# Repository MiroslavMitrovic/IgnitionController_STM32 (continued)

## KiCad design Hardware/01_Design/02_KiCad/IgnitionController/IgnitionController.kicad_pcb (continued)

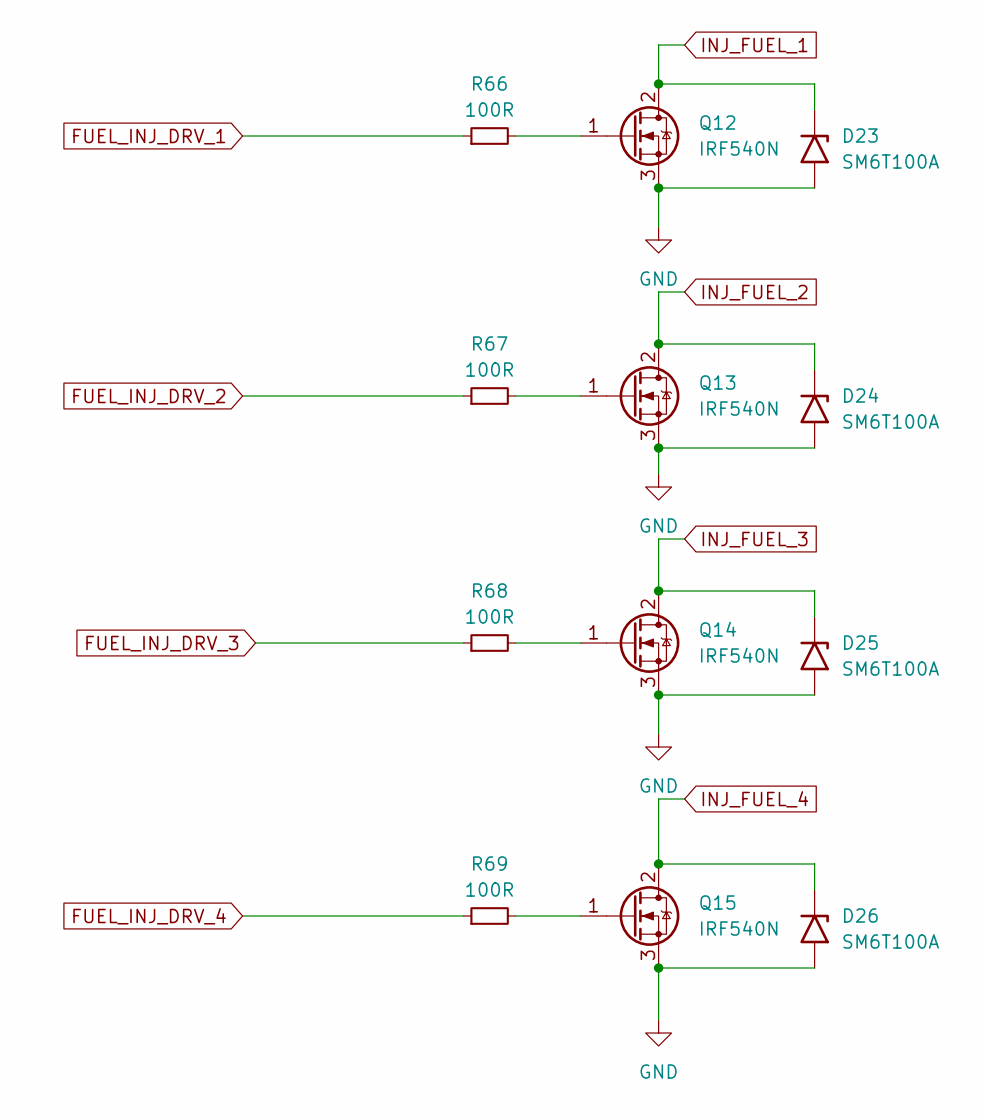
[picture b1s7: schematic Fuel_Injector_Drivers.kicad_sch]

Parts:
D23, D24, D25, D26: SM6T100A; D_SMB
Q12, Q13, Q14, Q15: IRF540N; TO-220-3_Vertical
R66, R67, R68, R69: 100R; R_0603_1608Metric_Pad0.98x0.95mm_HandSolder

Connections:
FUEL_INJ_DRV_1: R66.1; also elsewhere on the board
FUEL_INJ_DRV_2: R67.1
FUEL_INJ_DRV_3: R68.1; also elsewhere on the board
FUEL_INJ_DRV_4: R69.1; also elsewhere on the board
INJ_FUEL_1: D23.1 (A1), Q12.2 (D); also elsewhere on the board
INJ_FUEL_2: D24.1 (A1), Q13.2 (D); also elsewhere on the board
INJ_FUEL_3: D25.1 (A1), Q14.2 (D); also elsewhere on the board
INJ_FUEL_4: D26.1 (A1), Q15.2 (D); also elsewhere on the board
unnamed: Q12.1 (G), R66.2
unnamed: Q13.1 (G), R67.2
unnamed: Q14.1 (G), R68.2
unnamed: Q15.1 (G), R69.2

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
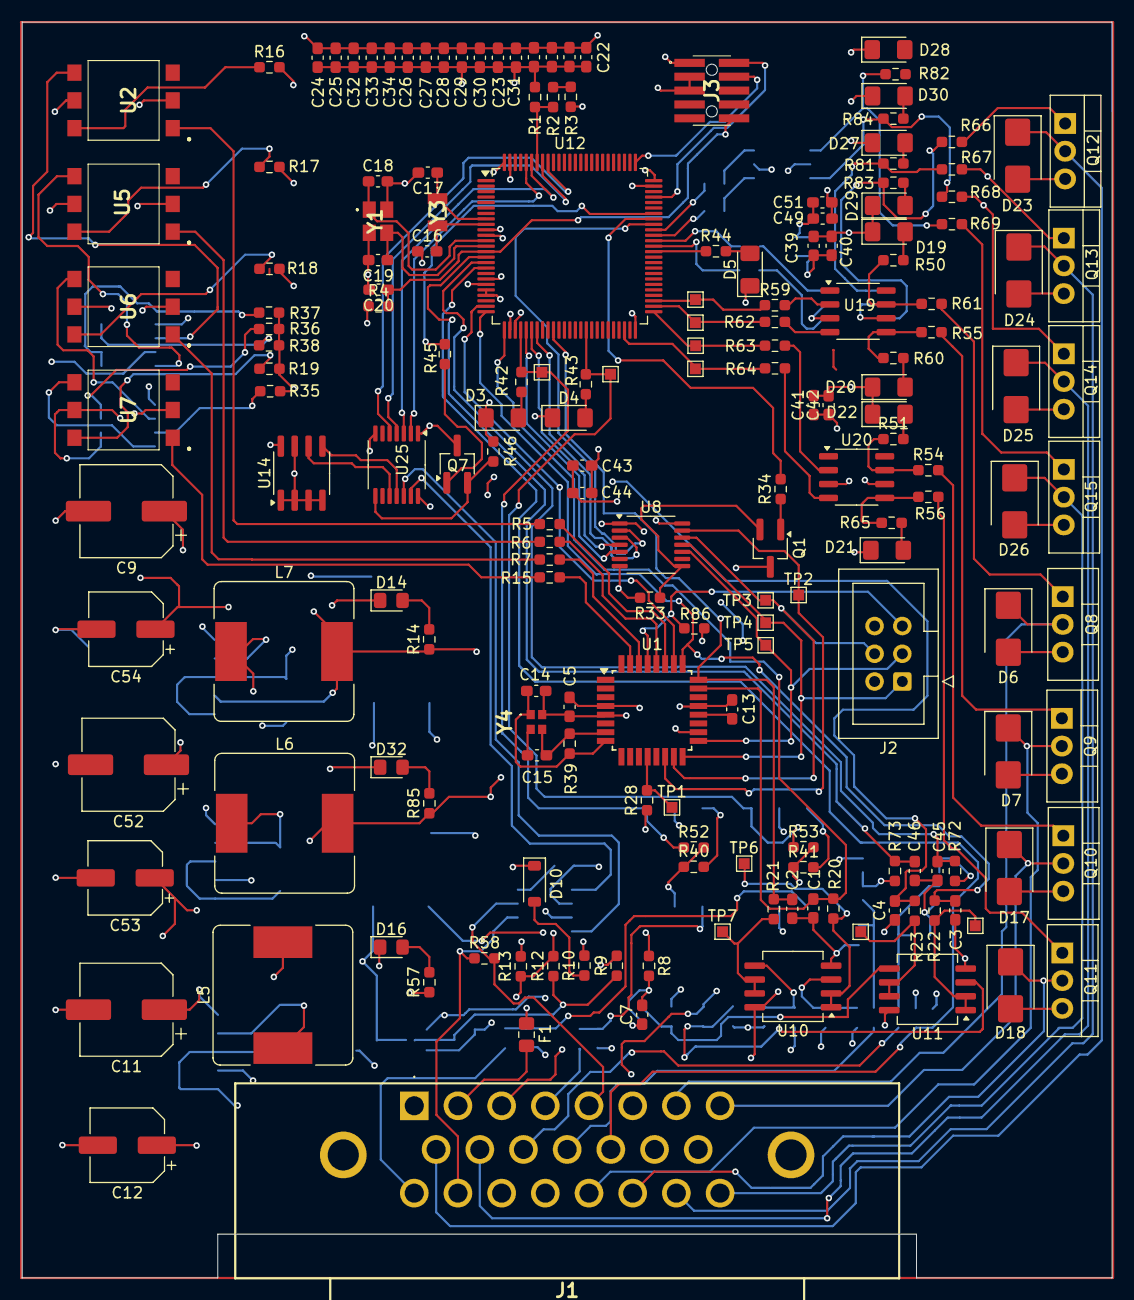
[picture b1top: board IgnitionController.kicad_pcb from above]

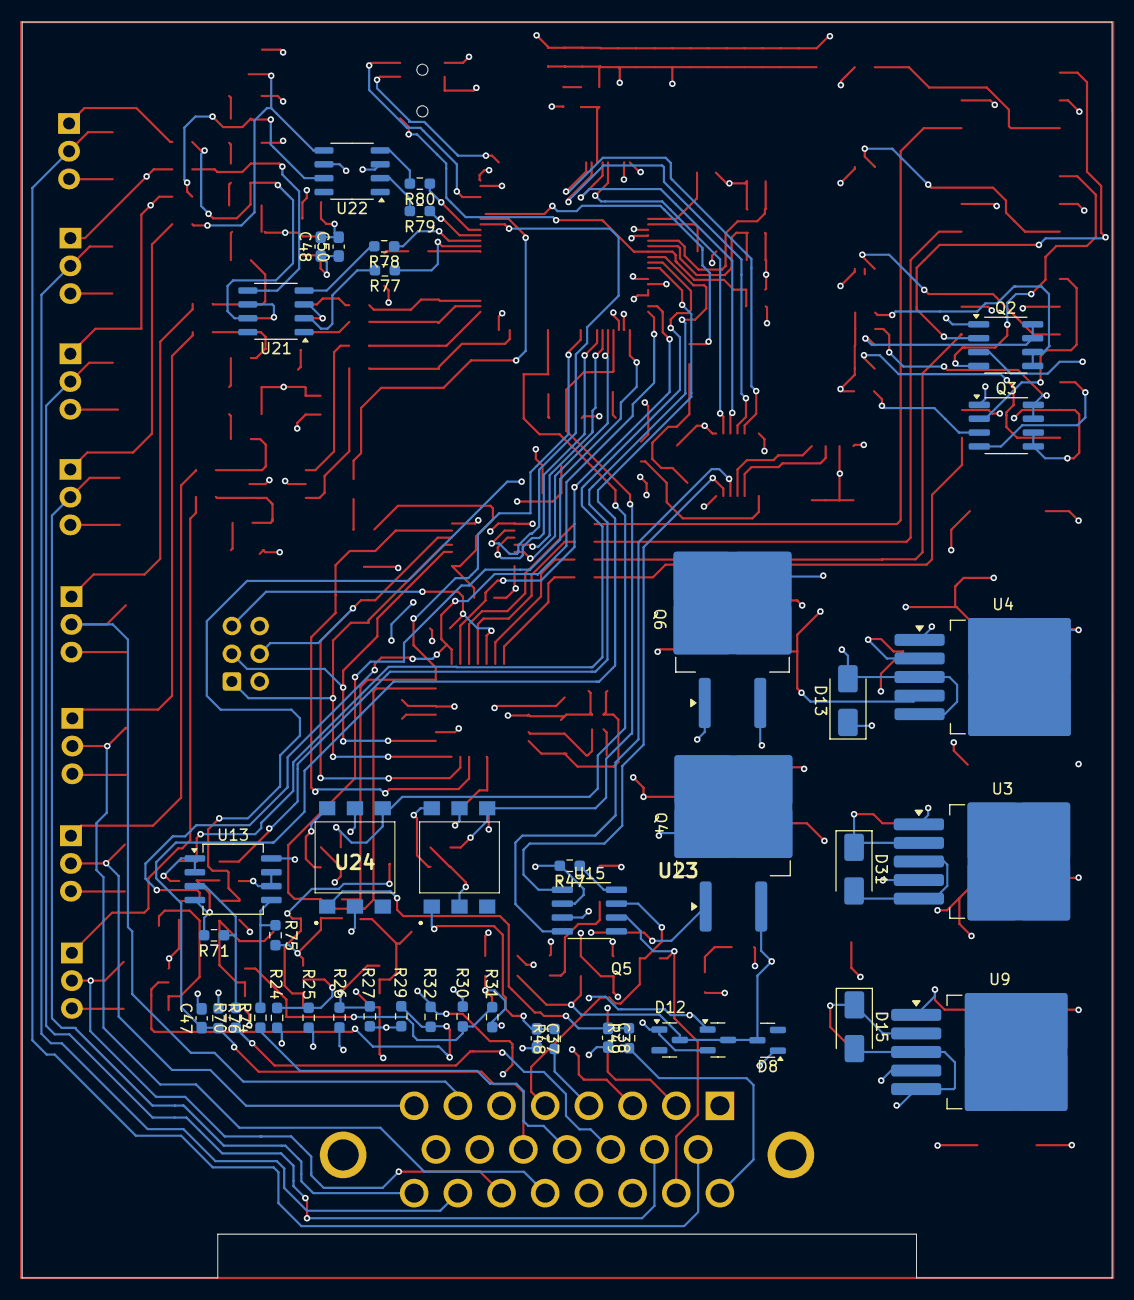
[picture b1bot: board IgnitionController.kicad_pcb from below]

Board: 4 copper layers, 99.8 x 115.0 mm, 226 parts (44 on the bottom side), 159 nets.

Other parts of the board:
R86: 10k; R_0603_1608Metric_Pad0.98x0.95mm_HandSolder
Y4: NX2016SA-16MHZ-EXS00A-CS07826; NX2016SA16MHZEXS00ACS07826

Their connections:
PMIC_RESET: R86.2; also elsewhere on the board
VPMIC: R86.1; also elsewhere on the board

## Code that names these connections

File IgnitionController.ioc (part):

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Mcu.Name=STM32F407V(E-G)Tx
Mcu.Package=LQFP100
Mcu.UserName=STM32F407VGTx
PA1.GPIOParameters=GPIO_Label
PA1.GPIO_Label=ADC_VMCU
PA1.Signal=ADCx_IN1
PA10.GPIOParameters=GPIO_Label
PA10.GPIO_Label=OE_PIN2
PA10.Signal=GPIO_Output
PA13.GPIOParameters=GPIO_Label
PA13.GPIO_Label=SWDIO
PA13.Mode=Serial_Wire
PA13.Signal=SYS_JTMS-SWDIO
PA14.GPIOParameters=GPIO_Label
PA14.GPIO_Label=SWCLK
PA14.Mode=Serial_Wire
PA14.Signal=SYS_JTCK-SWCLK
PA2.GPIOParameters=GPIO_Label
PA2.GPIO_Label=ADC_VSENS
PA2.Signal=ADCx_IN2
PA3.GPIOParameters=GPIO_Label
PA3.GPIO_Label=ADC_VBAT
PA3.Signal=ADCx_IN3
PA4.GPIOParameters=GPIO_PuPd,GPIO_Label
PA4.GPIO_Label=Signal1_IntPin
PA4.GPIO_PuPd=GPIO_PULLDOWN
PA4.Signal=GPXTI4
PA5.Mode=Full_Duplex_Master
PA5.Signal=SPI1_SCK
PA6.Mode=Full_Duplex_Master
PA6.Signal=SPI1_MISO
PA7.Mode=Full_Duplex_Master
PA7.Signal=SPI1_MOSI
PA8.GPIOParameters=GPIO_Label
PA8.GPIO_Label=SPI1_CS
PA8.Signal=GPIO_Output
PA9.GPIOParameters=GPIO_Label
PA9.GPIO_Label=OE_PIN1
PA9.Signal=GPIO_Output
PB0.GPIOParameters=GPIO_Label
PB0.GPIO_Label=ADC_IGNITION
PB0.Signal=ADCx_IN8
PB11.GPIOParameters=GPIO_Label
PB11.GPIO_Label=Cylinder4Out_Pin
PB11.Signal=GPIO_Output
PB12.GPIOParameters=GPIO_Label
PB12.GPIO_Label=Cylinder3Out_Pin
PB12.Signal=GPIO_Output
PB13.GPIOParameters=GPIO_Label
PB13.GPIO_Label=TestLED2
PB13.Signal=GPIO_Output
PB14.GPIOParameters=GPIO_Label
PB14.GPIO_Label=TestLED1
PB14.Signal=GPIO_Output
PB6.Mode=I2C
PB6.Signal=I2C1_SCL
PB7.Mode=I2C
PB7.Signal=I2C1_SDA
PB8.Mode=CAN_Activate
PB8.Signal=CAN1_RX
PB9.Mode=CAN_Activate
PB9.Signal=CAN1_TX
PC0.Signal=ADCx_IN10
PC1.Signal=ADCx_IN11
PC10.Mode=Asynchronous
PC10.Signal=USART3_TX
PC11.Mode=Asynchronous
PC11.Signal=USART3_RX
PC14-OSC32_IN.GPIOParameters=GPIO_Label
PC14-OSC32_IN.GPIO_Label=PC14-OSC32_IN
PC14-OSC32_IN.Mode=LSE-External-Oscillator
PC14-OSC32_IN.Signal=RCC_OSC32_IN
PC15-OSC32_OUT.GPIOParameters=GPIO_Label
PC15-OSC32_OUT.GPIO_Label=PC15-OSC32_OUT
PC15-OSC32_OUT.Mode=LSE-External-Oscillator
PC15-OSC32_OUT.Signal=RCC_OSC32_OUT
PC2.Signal=ADCx_IN12
PC6.Signal=S_TIM3_CH1
PC7.Signal=S_TIM3_CH2
PC8.Signal=S_TIM3_CH3
PC9.Signal=S_TIM3_CH4
PE10.GPIOParameters=GPIO_PuPd,GPIO_Label
PE10.GPIO_Label=Signal2_IntPin
PE10.GPIO_PuPd=GPIO_PULLDOWN
PE10.Signal=GPXTI10
PH0-OSC_IN.GPIOParameters=GPIO_Label
PH0-OSC_IN.GPIO_Label=PH0-OSC_IN
PH0-OSC_IN.Mode=HSE-External-Oscillator
PH0-OSC_IN.Signal=RCC_OSC_IN
PH1-OSC_OUT.GPIOParameters=GPIO_Label
PH1-OSC_OUT.GPIO_Label=PH1-OSC_OUT
PH1-OSC_OUT.Mode=HSE-External-Oscillator
PH1-OSC_OUT.Signal=RCC_OSC_OUT
RCC.HSE_VALUE=8000000
RCC.SYSCLKFreq_VALUE=168000000
RCC.SYSCLKSource=RCC_SYSCLKSOURCE_PLLCLK
board=STM32F407G-DISC1
boardIOC=true

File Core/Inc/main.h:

/* USER CODE BEGIN Header */
/**
  ******************************************************************************
  * @file           : main.h
  * @brief          : Header for main.c file.
  *                   This file contains the common defines of the application.
  ******************************************************************************
  * @attention
  *
  * Copyright (c) 2022 STMicroelectronics.
  * All rights reserved.
  *
  * This software is licensed under terms that can be found in the LICENSE file
  * in the root directory of this software component.
  * If no LICENSE file comes with this software, it is provided AS-IS.
  *
  ******************************************************************************
  */
/* USER CODE END Header */

/* Define to prevent recursive inclusion -------------------------------------*/
#ifndef __MAIN_H
#define __MAIN_H

#ifdef __cplusplus
extern "C" {
#endif

/* Includes ------------------------------------------------------------------*/
#include "stm32f4xx_hal.h"

/* Private includes ----------------------------------------------------------*/
/* USER CODE BEGIN Includes */
#include "IgnitionCotrol_Main.h"
/* USER CODE END Includes */

/* Exported types ------------------------------------------------------------*/
/* USER CODE BEGIN ET */

/* USER CODE END ET */

/* Exported constants --------------------------------------------------------*/
/* USER CODE BEGIN EC */

/* USER CODE END EC */

/* Exported macro ------------------------------------------------------------*/
/* USER CODE BEGIN EM */

/* USER CODE END EM */

void HAL_TIM_MspPostInit(TIM_HandleTypeDef *htim);

/* Exported functions prototypes ---------------------------------------------*/
void Error_Handler(void);

/* USER CODE BEGIN EFP */
void ITM_SendChar2(uint8_t ch);
/* USER CODE END EFP */

/* Private defines -----------------------------------------------------------*/
#define PC14_OSC32_IN_Pin GPIO_PIN_14
#define PC14_OSC32_IN_GPIO_Port GPIOC
#define PC15_OSC32_OUT_Pin GPIO_PIN_15
#define PC15_OSC32_OUT_GPIO_Port GPIOC
#define PH0_OSC_IN_Pin GPIO_PIN_0
#define PH0_OSC_IN_GPIO_Port GPIOH
#define PH1_OSC_OUT_Pin GPIO_PIN_1
#define PH1_OSC_OUT_GPIO_Port GPIOH
#define ADC_VMCU_Pin GPIO_PIN_1
#define ADC_VMCU_GPIO_Port GPIOA
#define ADC_VSENS_Pin GPIO_PIN_2
#define ADC_VSENS_GPIO_Port GPIOA
#define ADC_VBAT_Pin GPIO_PIN_3
#define ADC_VBAT_GPIO_Port GPIOA
#define Signal1_IntPin_Pin GPIO_PIN_4
#define Signal1_IntPin_GPIO_Port GPIOA
#define Signal1_IntPin_EXTI_IRQn EXTI4_IRQn
#define ADC_IGNITION_Pin GPIO_PIN_0
#define ADC_IGNITION_GPIO_Port GPIOB
#define Signal2_IntPin_Pin GPIO_PIN_10
#define Signal2_IntPin_GPIO_Port GPIOE
#define Signal2_IntPin_EXTI_IRQn EXTI15_10_IRQn
#define Cylinder4Out_Pin_Pin GPIO_PIN_11
#define Cylinder4Out_Pin_GPIO_Port GPIOB
#define Cylinder3Out_Pin_Pin GPIO_PIN_12
#define Cylinder3Out_Pin_GPIO_Port GPIOB
#define TestLED2_Pin GPIO_PIN_13
#define TestLED2_GPIO_Port GPIOB
#define TestLED1_Pin GPIO_PIN_14
#define TestLED1_GPIO_Port GPIOB
#define SPI1_CS_Pin GPIO_PIN_8
#define SPI1_CS_GPIO_Port GPIOA
#define OE_PIN1_Pin GPIO_PIN_9
#define OE_PIN1_GPIO_Port GPIOA
#define OE_PIN2_Pin GPIO_PIN_10
#define OE_PIN2_GPIO_Port GPIOA
#define SWDIO_Pin GPIO_PIN_13
#define SWDIO_GPIO_Port GPIOA
#define SWCLK_Pin GPIO_PIN_14
#define SWCLK_GPIO_Port GPIOA

/* USER CODE BEGIN Private defines */

/* USER CODE END Private defines */

#ifdef __cplusplus
}
#endif

#endif /* __MAIN_H */

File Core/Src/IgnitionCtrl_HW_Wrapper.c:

/**
 * @file      IgnitionCtrl_HW_Wrapper.c
 * @authors   Miroslav Mitrovic
 * Created on September 16, 2022, 7:33 PM
 * @Copyright 2022 by Miroslav Mitrovic <mmitrovicmas13@gmail.com>
 *
 * This file is part of open source application.
 * 
 * Open source application is free software: you can redistribute 
 * it and/or modify it under the terms of the GNU General Public 
 * License as published by the Free Software Foundation, either 
 * version 3 of the License, or (at your option) any later version.
 * 
 * Open source application is distributed in the hope that it will 
 * be useful, but WITHOUT ANY WARRANTY; without even the implied warranty 
 * of MERCHANTABILITY or FITNESS FOR A PARTICULAR PURPOSE.  See the
 * GNU General Public License for more details.
 * 
 * You should have received a copy of the GNU General Public License
 * along with this application.  If not, see <http://www.gnu.org/licenses>.
 *
 * @license GPL-3.0+ <http://spdx.org/licenses/GPL-3.0+>
 *
 * @brief [description]
 */
/*******************************************************************************
 * Includes
 *******************************************************************************/
#include "IgnitionCotrol_Main.h"
/*******************************************************************************
 * Defines
 *******************************************************************************/

/*******************************************************************************
 * Local Types and Typedefs
 *******************************************************************************/

/*******************************************************************************
 * Global Variables
 *******************************************************************************/
 volatile uint32_t g_usSinceDetectionCyl1;
 volatile uint32_t g_usSinceDetectionCyl2;
 volatile uint32_t g_uSCounter;
 volatile uint32_t g_uSDebouncingSignalCounter;
 volatile uint8_t  g_signalDebouncingTimerStarted;
/*******************************************************************************
 * Static Function Prototypes
 *******************************************************************************/

/*******************************************************************************
 * Static Variables
 *******************************************************************************/

/*******************************************************************************
 * Functions
 *******************************************************************************/
void HW_GPIO_v_Init(void)
{
#ifdef ATMEL_MCU
  /*Set Pins 5 and 6 as Output High */
DDRB |= ((1 << PB1) | (1 << PB0) | (1 << PB2) | (1 << PB3) | (1 << PB4)) | (1 << PB5);
/*Set Pins 3 and 2 as Input pins*/
DDRB &= (~(1 << PB3) & ~(1 << PB2) );
DDRB |= (1 << PB4);
PORTB &= ~(1 << PB1 );
PORTB &= ~(1 << PB0 );
#else
/*TODO: Implement STM32Fxx handling of GPIO INIT*/
#endif /*ATMEL_MCU*/
}

void HW_Timer_v_Init(void)
{
#ifdef ATMEL_MCU
    TCCR0B |= (1 << CS00);   	//Select the clock source-Internal Oscillator clk_io/8 = 1MHz ClockDivider is C00(no divsion) - overflow happens at 256uS(counts)
	TCNT0 = 0;
	TIMSK |=  (1 << TOIE0);				//Enable Timer0 overflow interrupt
#else
/*TODO: Implement STM32Fxx handling of Timer INIT*/
#endif /*ATMEL_MCU*/
	g_uSCounter = 0;
	g_usSinceDetectionCyl1 = 0;
	g_uSDebouncingSignalCounter = 0;
}

void HW_FiringPin_v_Cylinder_1_Set(void)
{
#ifdef ATMEL_MCU
	PORTB |= ( 1<< PB1);
#else
	// HAL_GPIO_WritePin(GPIOD, LD4_Pin, GPIO_PIN_SET);
	HAL_GPIO_WritePin(TestLED1_GPIO_Port, TestLED1_Pin, GPIO_PIN_SET);
#endif /*ATMEL_MCU*/


}

void HW_FiringPin_v_Cylinder_1_Reset(void)
{
#ifdef ATMEL_MCU
    PORTB &= ~( 1<< PB1);
#else
	// HAL_GPIO_WritePin(GPIOD, LD4_Pin, GPIO_PIN_RESET);
	HAL_GPIO_WritePin(TestLED1_GPIO_Port, TestLED1_Pin, GPIO_PIN_RESET);
#endif /*ATMEL_MCU*/
}

void HW_FiringPin_v_Cylinder_2_Set(void)
{
#ifdef ATMEL_MCU
	PORTB |= ( 1<< PB0);
#else
	HAL_GPIO_WritePin(TestLED2_GPIO_Port, TestLED2_Pin, GPIO_PIN_SET);
#endif /*ATMEL_MCU*/
}

void HW_FiringPin_v_Cylinder_2_Reset(void)
{
#ifdef ATMEL_MCU
    PORTB &= ~( 1<< PB0);
#else
	HAL_GPIO_WritePin(TestLED2_GPIO_Port, TestLED2_Pin, GPIO_PIN_RESET);
#endif /*ATMEL_MCU*/
}

GPIO_PinState HW_FiringPin_v_Cylinder_1_Status_Read(void)
{
	return	HAL_GPIO_ReadPin(TestLED1_GPIO_Port,TestLED1_Pin);
}

GPIO_PinState HW_FiringPin_v_Cylinder_2_Status_Read(void)
{
	//HAL_GPIO_ReadPin(TestLED1_GPIO_Port,TestLED1_Pin);
}

#ifdef STM32_MCU
void HAL_GPIO_EXTI_Callback(uint16_t GPIO_Pin)
{
	/* Prevent unused argument(s) compilation warning */
	if(Signal1_IntPin_Pin == GPIO_Pin)
	{
		if(5U < g_uSDebouncingSignalCounter) /* Check if the signal was triggered in time less than 50uS */
		{
			IgnitionControl_v_UpdateSignalTime();
	/* 		g_uSDebouncingSignalCounter = 0;
			g_signalDebouncingTimerStarted = 1; */
		}
	}
	else if (Signal2_IntPin_Pin == GPIO_Pin)
	{
		if(5U < g_uSDebouncingSignalCounter) /* Check if the signal was triggered in time less than 50uS */
		{
			IgnitionControl_v_UpdateSignalTimeCylinder2();
			g_uSDebouncingSignalCounter = 0;
			g_signalDebouncingTimerStarted = 1;
			
		}
	}
	else{}
  /* NOTE: This function Should not be modified, when the callback is needed,
           the HAL_GPIO_EXTI_Callback could be implemented in the user file
   */
}
#endif /* STM32_MCU */

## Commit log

2022-11-25 initial File commit
2022-11-25 comments removed
2022-11-25 Added new line
2022-12-23 Create LICENSE
2022-12-23 Implemented First Cylinder Firing
2022-12-23 Added Design folder
2022-12-23 Added documentation folder
2022-12-23 Initial Architecture and Design
2022-12-25 Doubled tst_GlobalData GlobalDataValues variable fix
2022-12-25 Added .srec file, cleanup script for Debug files
2022-12-25 Removal of debug files
2022-12-27 Added .gitignore file
2023-02-28 Added Dynamic Tests-GTest Framework
2023-03-01 Documentation updates
2023-03-25 Updates to Gitignore file
2023-03-25 Additional ignored files and folders for CMake build
2023-03-25 Removal of leftover build files
2023-03-25 Adding of CMake build toolchain
2023-03-25 Additional updates to .gitignore file
2023-03-25 removal of STM32CubeIDE files
2023-03-25 Updates to STM32Cube IOC file
2023-03-25 Updates to readme. Added Cmake Toolchain commands
2023-03-25 Fixes To the readme
2023-03-25 Updates to Compiler Warning Flags
2023-03-25 Added macro check for polyspace tool
2023-03-25 Initial Batch script for performing Static Code Analysis with Polyspace
2023-03-25 Added new folders for Static Tests to gitignore
2023-03-25 Added command for opening the report and project in Polyspace GUI
2023-07-21 Update README.md
    Added Testing Folder Decsription
2023-10-04 Added macros for different calculations
2023-10-07 MCU datasheet,reference manual and HAL&LL Driver description
2023-10-07 Updates to gitignore file, added build folder of GTest Framework
2023-10-07 removal of GTest Framework build files
2023-10-07 Updated the testcode for Math.h library if VS or other compiler is used
2023-10-07 "Configured SigPin1 and SigPin2 as Interrupts.
2023-10-07 Added build script
2023-10-07 Added linker command for ending the linking group
2025-02-15 Linker configuration fix
2025-02-15 Fixes to cmakelists.txt
2025-02-16 Updated build script to support timing of build process.
2025-02-20 Update RPM calculation method
2025-03-02 Implemented firing logic for engine cranking case
2025-03-02 RPM Hard Limit implementation
2025-03-16 Fix for cranking handling
2025-03-19 Fixes for handling Transition
2025-03-20 Configuration and RPM filtering fixes
2025-03-21 2ndCylinder firing implemented
2025-03-26 2nd Cylinder Cranking Implementation
2025-03-29 Implemented proper 2nd cylinder firing logic
2025-04-05 Initial HW commit
2025-04-05 Added dummyFiles for Folder structure
2025-04-23 PowerSupply Initial Sch
2025-04-27 PMIC HW implementation
2025-04-28 Updated sch and footprints
2025-04-29 Added ROM/RAM calculation output
2025-05-01 MCU sheet Initial commit
2025-05-03 HAL Configuration updates
2025-05-03 Updates to cubeMX configuration
2025-05-03 Peripherals Update
2025-05-13 Updates to HW Layout
2025-05-13 Updates to generated code to accomodate latest HW changes
2025-05-13 IOC updates
2025-05-24 Initial routing of Power supply
2025-06-07 Added Crystal to PMIC
2025-06-07 MCU HW Initial Layout
2025-06-08 Added Peripheral HW Components
2025-06-08 Routing PCB done
2025-06-08 Updated Solder Mask labels
2025-06-12 Addition of 3d model of ECU
2025-12-27 Added Jenkinsfile
2025-12-27 Removed CAN init Function
2025-12-27 fixes to the toolchain paths
2025-12-27 Added CAN init function
2025-12-27 Initial plan
2025-12-27 Added CI Unit test
2025-12-27 Updated Jenkinsfile names
2025-12-27 Updated unit test
2025-12-27 Fixed Unit test
2025-12-30 uploaded jenkinsfile
